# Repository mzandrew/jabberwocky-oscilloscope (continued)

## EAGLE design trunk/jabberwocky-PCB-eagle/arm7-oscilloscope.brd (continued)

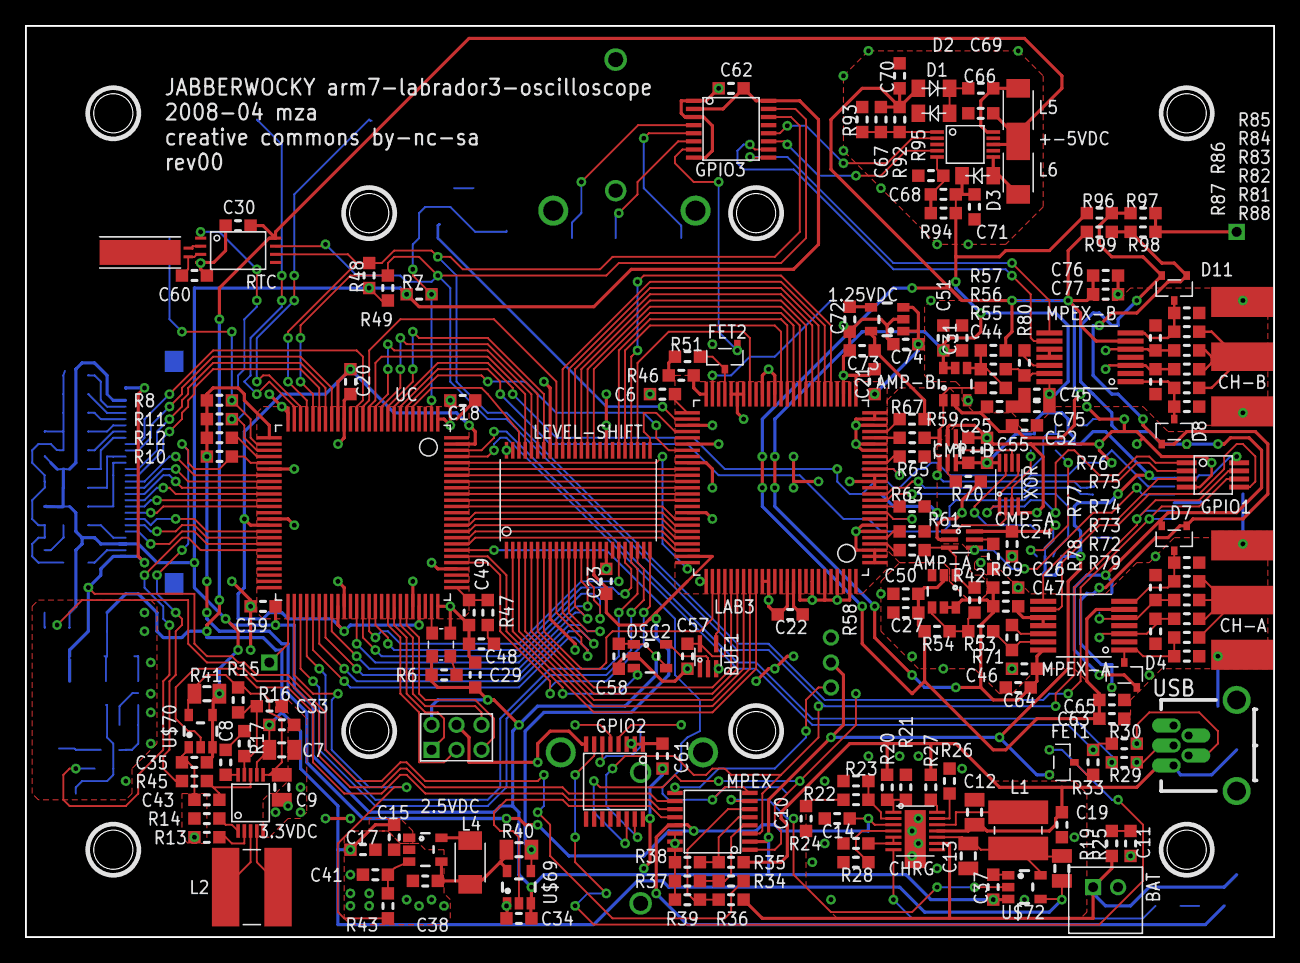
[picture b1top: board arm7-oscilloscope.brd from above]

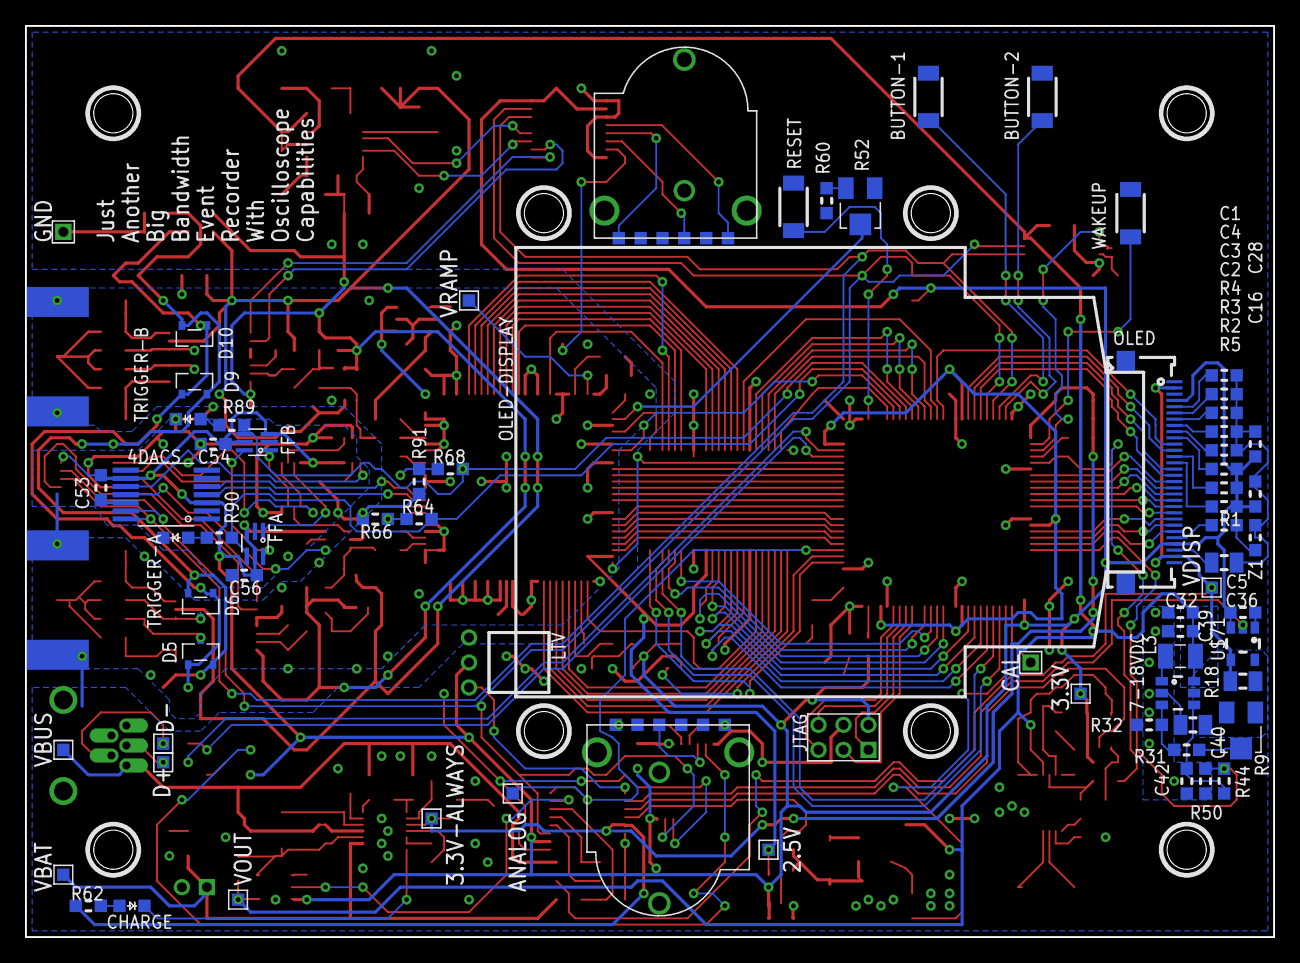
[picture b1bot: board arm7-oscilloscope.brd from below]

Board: 2 copper layers, 100.0 x 73.0 mm, 266 parts (79 on the bottom side), 222 nets.

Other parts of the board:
OLED-DISPLAY: OLED-DISPLAY-OUTLINE-UNFURLED
U$6, U$37, U$59, U$77, U$176, U$177, U$178, U$179: MOUNTING-HOLE-4-40-SHCS

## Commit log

2008-05-04 Initial directory structure.
2009-03-14 Created wiki page through web user interface.
2009-03-14 Edited wiki page through web user interface.
2015-08-12 well, google code is going readonly soon, so I guess I'd better finally post this stuff
2015-08-17 made 3d model of PCB and designed case around it (solidworks2014); added timing diagram scans; added images of first data acquired (hexdump) and first trace displayed (jpeg); updated eagle files to x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
2015-08-17 added a couple of images of the device in operation; added lowres images
2016-01-14 Migrating wiki contents from Google Code
2018-12-07 much easier these days to get this to work
2018-12-07 minor fix
2020-07-17 minor updates
